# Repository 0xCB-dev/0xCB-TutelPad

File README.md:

# 0xcb-TutelPad
## An 8-key macropad with a 128x64 pixel OLED display

Licence | OSHWA
:-------------------------:|:-------------------------:
 | 

### Available here:

[KeebSupply](https://keeb.supply/products/0xcb-tutelpad)

### QMK

[keyboards/0xcb/tutelpad/](https://github.com/qmk/qmk_firmware/tree/master/keyboards/0xcb/tutelpad)

#### Flashing

* `qmk clone`
* `cd qmk_firmware`
* `export LTO=Y`
* Press switch 1 while plugging in to go into dfu mode (or the reset button)
* `make 0xcb/tutelpad:via:flash`

### Assembly:

You can use the [humanpnp](https://files.0xcb.dev/0xCB-TutelPad/humanpnp.html) to easily place components.

### PCB:
KiCad 6 stable release - using these [libs](https://github.com/0xCB-dev/0xcb-libs)

Top | Bottom
:-------------------------:|:-------------------------:
  |  

### CAD files:

[DXF](https://github.com/0xCB-dev/0xCB-TutelPad/tree/main/CAD/DXF)

#### BOM:
 References                        | Value          | Quantity | Part Nb.            
-----------------------------------|----------------|----------|---------------------
 SW1                               | SPST RA        | 1        | C115343             
 RGB4,RGB3,RGB2,RGB1               | WS2812B        | 4        | C114586             
 OL1                               | SSD1306-128x64 | 1        | amazon

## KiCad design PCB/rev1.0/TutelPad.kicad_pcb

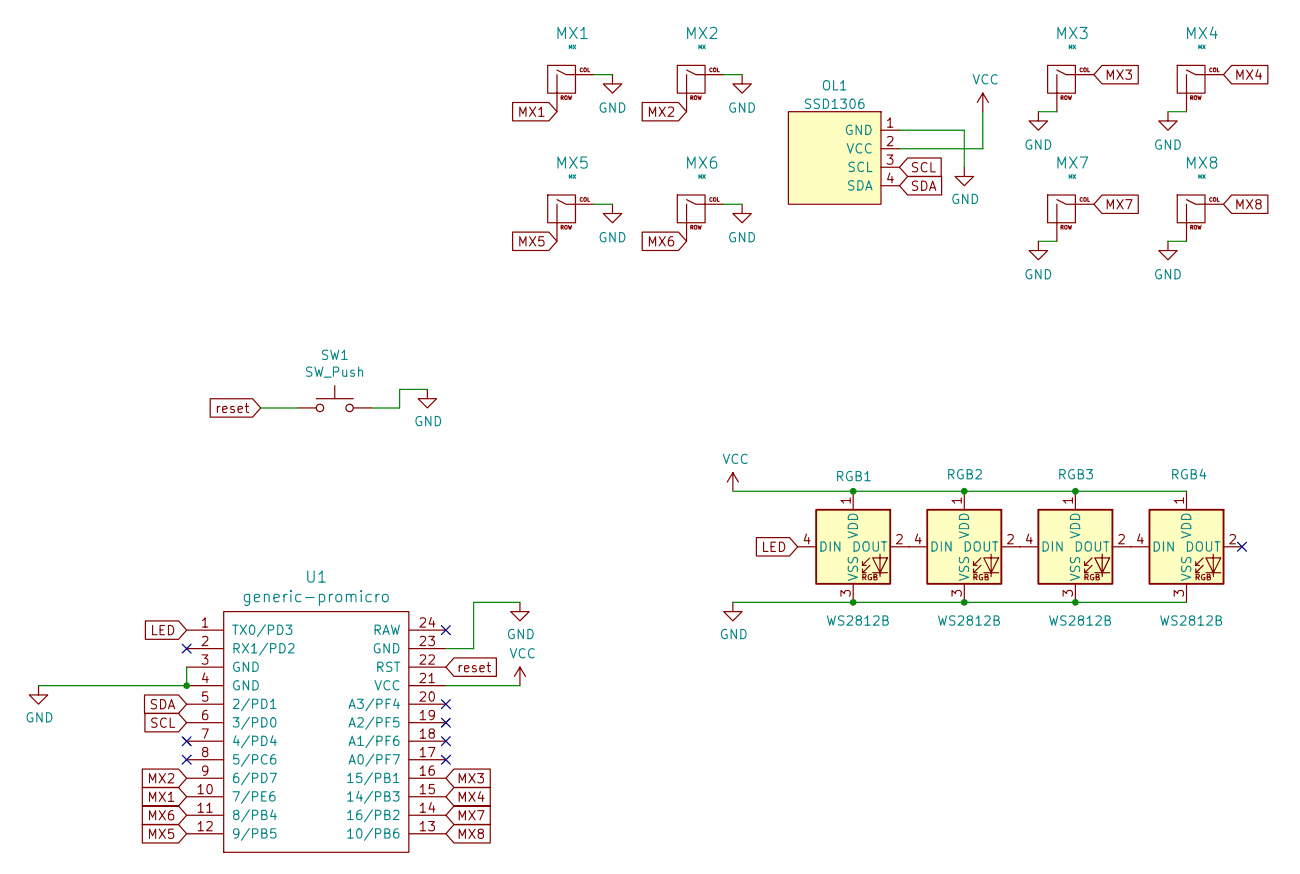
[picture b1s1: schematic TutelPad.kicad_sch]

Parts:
MX1, MX2, MX3, MX4, MX5, MX6, MX7, MX8: MX; SW_Cherry_MX_PCB_1.00u
OL1: SSD1306; 128x64OLED
RGB1, RGB2, RGB3, RGB4: WS2812B; LED_WS2812B_PLCC4_5.0x5.0mm_P3.2mm
SW1: SW_Push; SW_Tactile_SPST_Angled
U1: generic-promicro

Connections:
GND: MX1.1 (COL), MX2.1 (COL), MX3.2 (ROW), MX4.2 (ROW), MX5.1 (COL), MX6.1 (COL), MX7.2 (ROW), MX8.2 (ROW), OL1.1 (GND), RGB1.3 (VSS), RGB2.3 (VSS), RGB3.3 (VSS), RGB4.3 (VSS), SW1.2, U1.3 (GND), U1.4 (GND), U1.23 (GND)
LED: RGB1.4 (DIN), U1.1 (TX0/PD3)
MX1: MX1.2 (ROW), U1.10 (7/PE6)
MX2: MX2.2 (ROW), U1.9 (6/PD7)
MX3: MX3.1 (COL), U1.16 (15/PB1)
MX4: MX4.1 (COL), U1.15 (14/PB3)
MX5: MX5.2 (ROW), U1.12 (9/PB5)
MX6: MX6.2 (ROW), U1.11 (8/PB4)
MX7: MX7.1 (COL), U1.14 (16/PB2)
MX8: MX8.1 (COL), U1.13 (10/PB6)
unnamed: RGB1.2 (DOUT), RGB2.4 (DIN)
unnamed: RGB2.2 (DOUT), RGB3.4 (DIN)
unnamed: RGB3.2 (DOUT), RGB4.4 (DIN)
SCL: OL1.3 (SCL), U1.6 (3/PD0)
SDA: OL1.4 (SDA), U1.5 (2/PD1)
VCC: OL1.2 (VCC), RGB1.1 (VDD), RGB2.1 (VDD), RGB3.1 (VDD), RGB4.1 (VDD), U1.21 (VCC)
reset: SW1.1, U1.22 (RST)

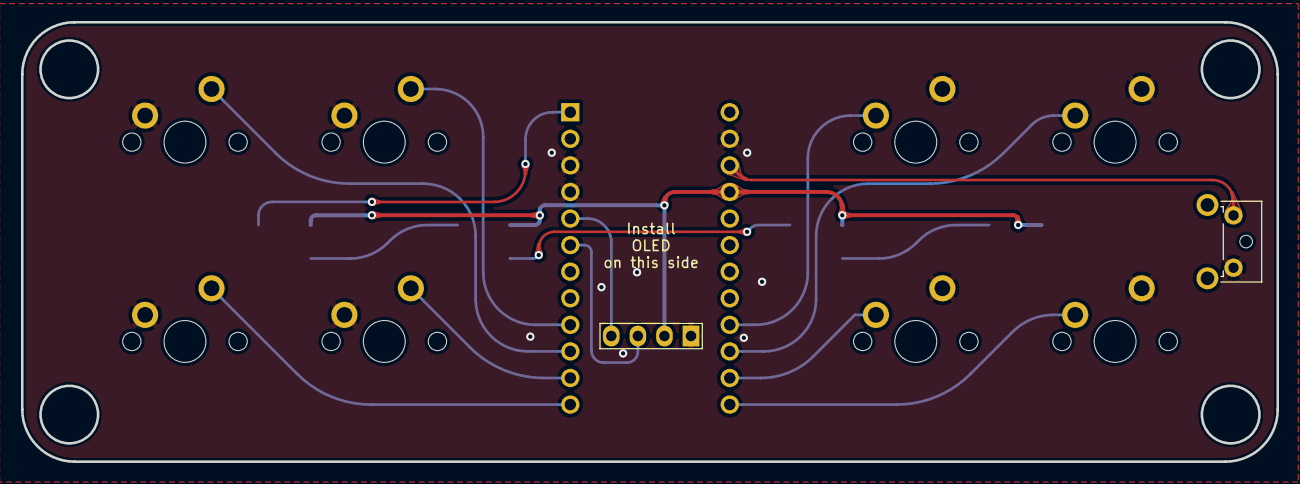
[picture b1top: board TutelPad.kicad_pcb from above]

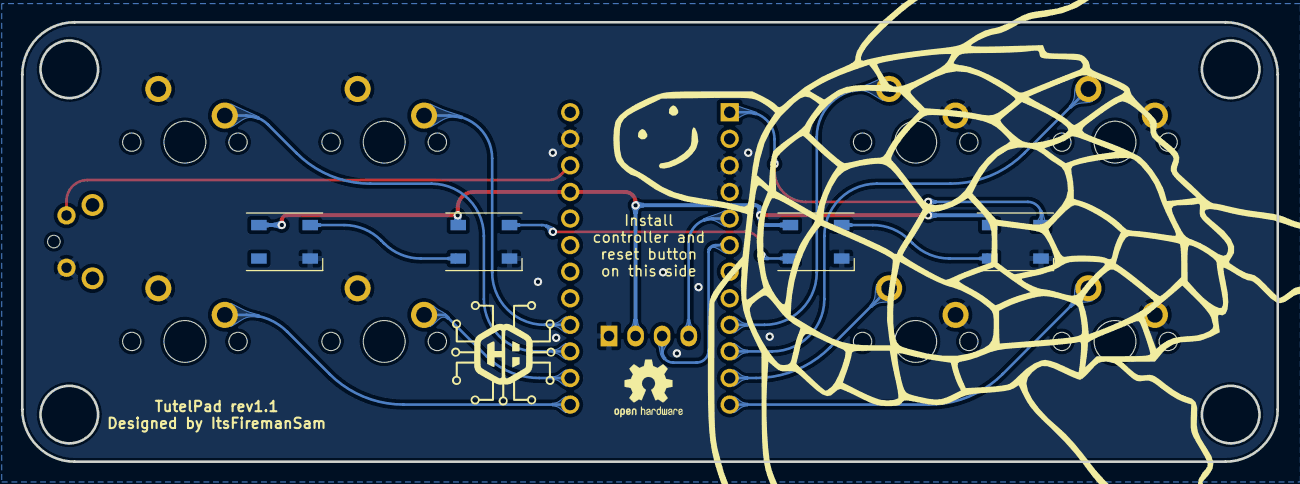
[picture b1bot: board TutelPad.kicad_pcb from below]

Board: 2 copper layers, 120.0 x 42.0 mm, 15 parts (4 on the bottom side), 17 nets.

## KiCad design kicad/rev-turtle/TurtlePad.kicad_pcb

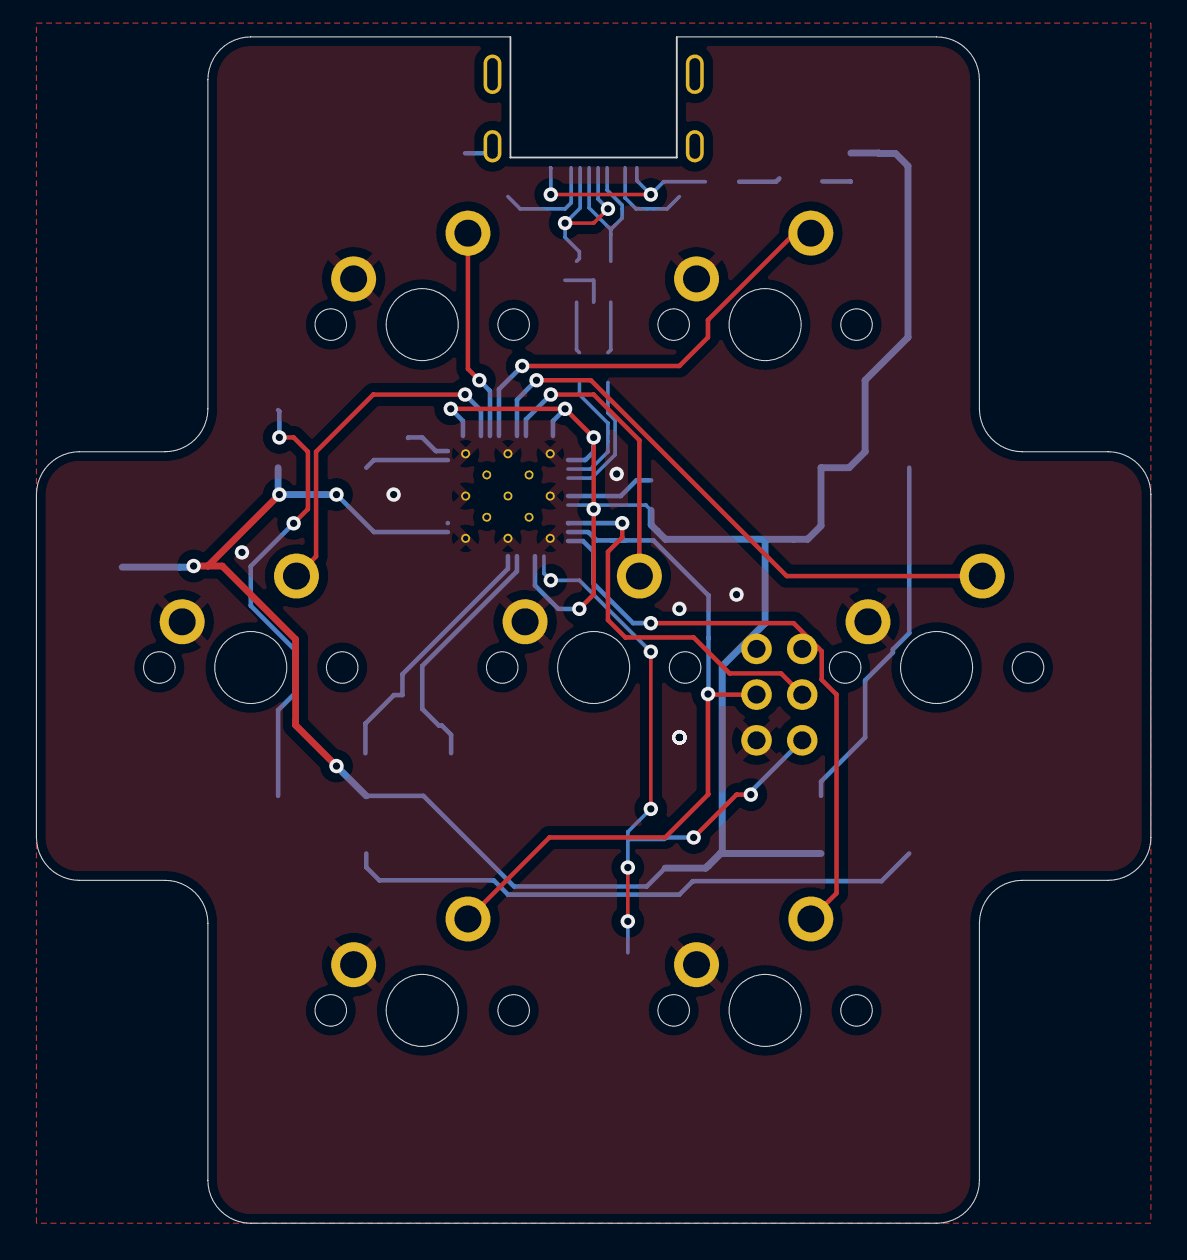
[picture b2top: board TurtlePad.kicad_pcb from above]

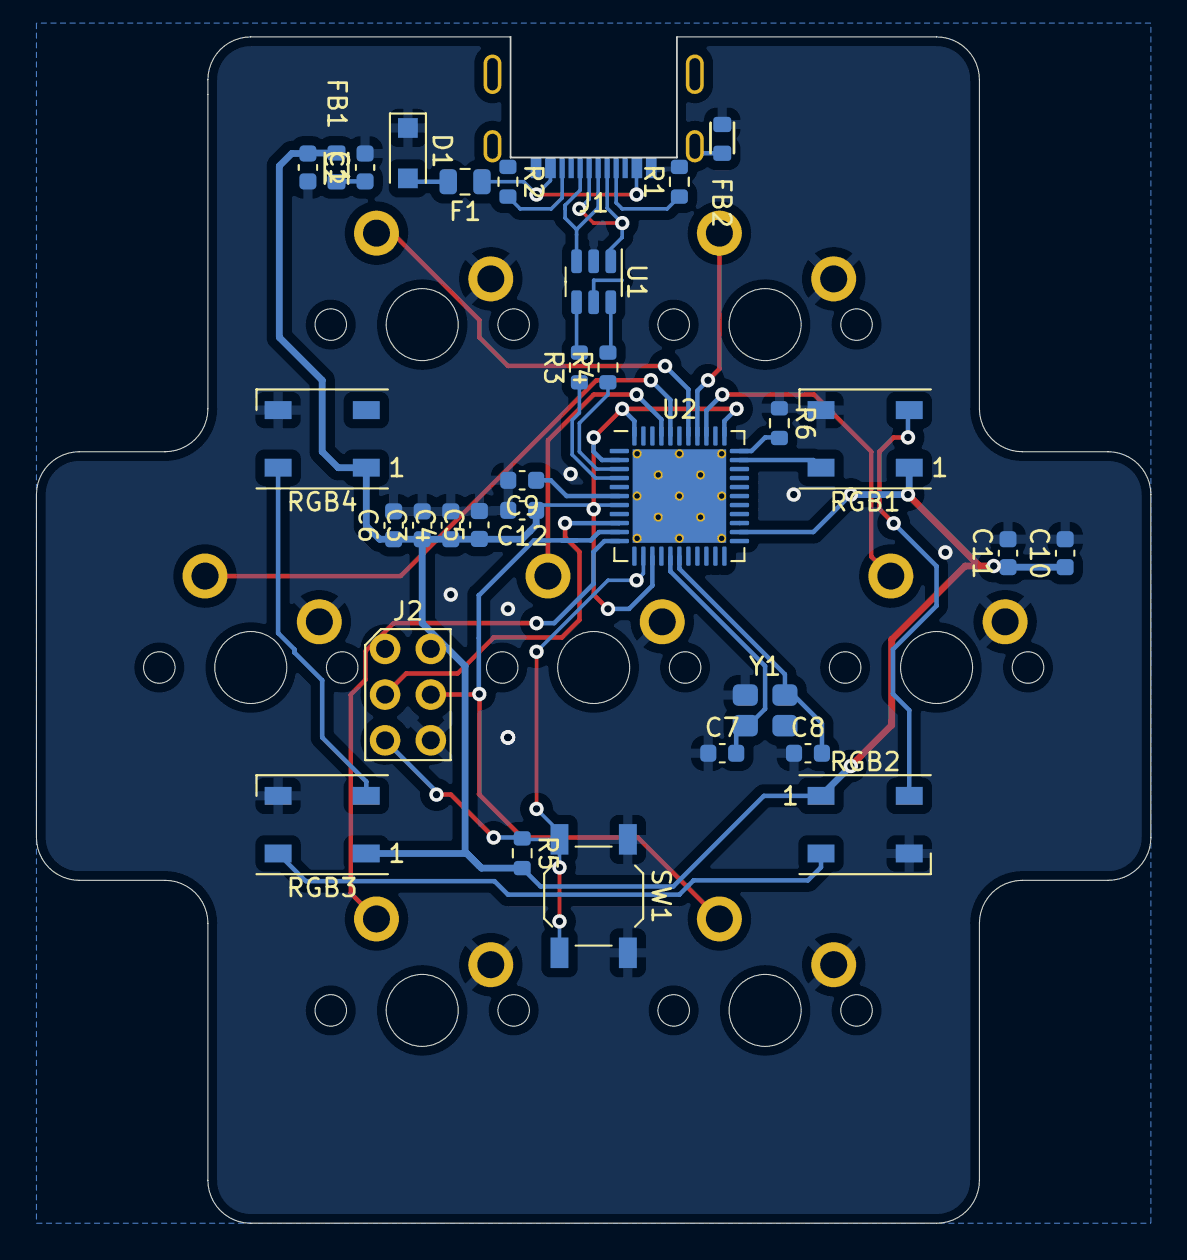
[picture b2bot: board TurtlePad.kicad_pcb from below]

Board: 2 copper layers, 61.9 x 65.9 mm, 39 parts (32 on the bottom side), 30 nets.

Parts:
C1: 10u; C_0603_1608Metric
C2, C6, C12: 1u; C_0603_1608Metric
C3, C4, C5, C9, C10, C11: 100n; C_0603_1608Metric
C7, C8: 22p; C_0603_1608Metric
D1: SMF5.0CA; D_SOD-123F
F1: 1A; Fuse_0805_2012Metric
FB1, FB2: 600R; Ferrite_Bead_0603
J1: USB_IN; molex2169900001
J2: AVR-ISP-6; AVR_PROG_2.54_THT
MX1, MX2, MX3, MX4, MX5, MX6, MX7: MX-NoLED; SW_Cherry_MX_PCB_1.00u
R1, R2: 5.1k; R_0603_1608Metric
R3, R4: 22; R_0603_1608Metric
R5, R6: 10k; R_0603_1608Metric
RGB1, RGB2, RGB3, RGB4: WS2812B; LED_WS2812B_PLCC4_5.0x5.0mm_P3.2mm
SW1: SW_Push; SW_SPST_TL3342
U1: USBLC6-2SC6; SOT-23-6
U2: ATMEGA32U4; QFN-44-1EP_7x7mm_P0.5mm_EP5.2x5.2mm_ThermalVias
Y1: 16MHz; Crystal_SMD_3225-4Pin_3.2x2.5mm

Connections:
/MCU+: R3.1, U2.4 (D+)
/MCU-: R4.1, U2.3 (D-)
/VBUS: F1.1, J1.A4 (VBUS), J1.A9 (VBUS), J1.B4 (VBUS), J1.B9 (VBUS), U1.5 (VBUS)
D+: R3.2, U1.4 (IO2)
D-: R4.2, U1.6 (IO1)
GND: C1.2, C2.2, C3.2, C4.2, C5.2, C6.2, C7.1, C8.1, C9.2, C10.2, C11.2, C12.2, D1.1 (A1), FB2.1, J1.A1 (GND), J1.A12 (GND), J1.B1 (GND), J1.B12 (GND), J2.6 (GND), MX1.1 (COL), MX2.1 (COL), MX3.1 (COL), MX4.1 (COL), MX5.1 (COL), MX6.1 (COL), MX7.1 (COL), R1.2, R2.1, R6.1, RGB1.3 (VSS), RGB2.3 (VSS), RGB3.3 (VSS), RGB4.3 (VSS), SW1.1, U1.2 (GND), U2.5 (UGnd), U2.15 (GND), U2.23 (GND), U2.35 (GND), U2.43 (GND), U2.45 (EP), Y1.2, Y1.4
LED: RGB1.4 (DIN), U2.32 (PC7)
MX1: MX1.2 (ROW), U2.37 (PF6)
MX2: MX2.2 (ROW), U2.38 (PF5)
MX3: MX3.2 (ROW), U2.36 (PF7)
MX4: MX4.2 (ROW), U2.41 (PF0)
MX5: MX5.2 (ROW), U2.40 (PF1)
MX6: J2.4 (MOSI), MX6.2 (ROW), U2.10 (PB2/MOSI)
MX7: J2.1 (MISO), MX7.2 (ROW), U2.11 (PB3/MISO)
unnamed: C1.1, D1.2 (A2), F1.2, FB1.1
unnamed: C7.2, U2.16 (XTAL1), Y1.1
unnamed: C8.2, U2.17 (XTAL2), Y1.3
unnamed: C9.1, U2.6 (UCap)
unnamed: FB2.2, J1.S1 (SHIELD)
unnamed: J1.A5 (CC1), R1.1
unnamed: J1.A6 (D+), J1.B6 (D+), U1.3 (IO2)
unnamed: J1.A7 (D-), J1.B7 (D-), U1.1 (IO1)
unnamed: J1.B5 (CC2), R2.2
unnamed: R6.2, U2.33 (PE2/~HWB)
unnamed: RGB1.2 (DOUT), RGB2.4 (DIN)
unnamed: RGB2.2 (DOUT), RGB3.4 (DIN)
unnamed: RGB3.2 (DOUT), RGB4.4 (DIN)
RST: J2.5 (~RST), R5.1, SW1.2, U2.13 (~RESET)
SCK: J2.3 (SCK), U2.9 (PB1/SCK), U2.20 (PD2)
VCC: C2.1, C3.1, C4.1, C5.1, C6.1, C10.1, C11.1, C12.1, FB1.2, J2.2 (VCC), R5.2, RGB1.1 (VDD), RGB2.1 (VDD), RGB3.1 (VDD), RGB4.1 (VDD), U2.2 (UVcc), U2.7 (VBus), U2.14 (VCC), U2.24 (AVCC), U2.34 (VCC), U2.44 (AVCC)

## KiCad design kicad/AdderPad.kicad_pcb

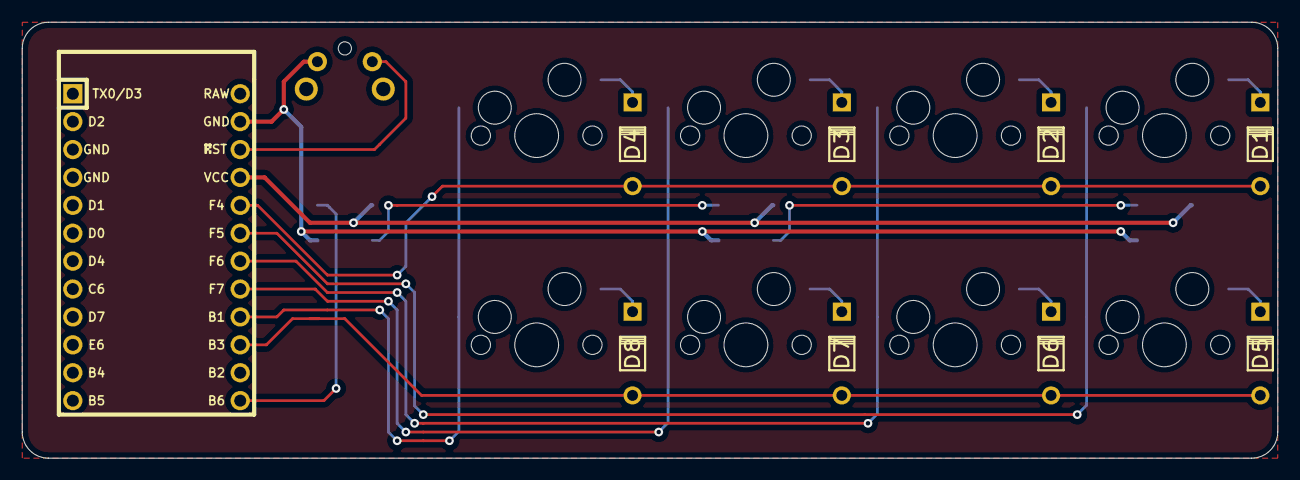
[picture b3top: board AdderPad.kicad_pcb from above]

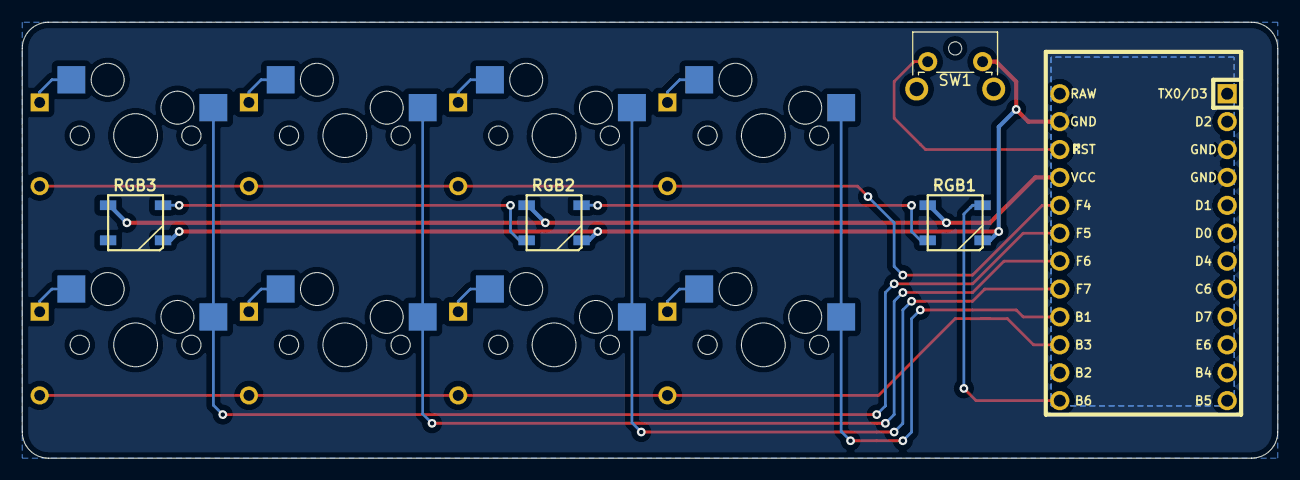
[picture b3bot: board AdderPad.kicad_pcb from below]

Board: 2 copper layers, 114.3 x 39.7 mm, 21 parts (4 on the bottom side), 20 nets.

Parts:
D1, D2, D3, D4, D5, D6, D7, D8: D_Small; Diode
MX1, MX2, MX3, MX4, MX5, MX6, MX7, MX8: MX-NoLED; MXOnly-1U-Hotswap
RGB1, RGB2, RGB3: WS2812B
SW1: SW_Push; SW_Tactile_SPST_Angled_MJTP1117
U1: ProMicro; ArduinoProMicro

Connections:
COL0: MX1.1, MX5.1, U1.19
COL1: MX2.1, MX6.1, U1.18
COL2: MX3.1, MX7.1, U1.17
COL3: MX4.1, MX8.1, U1.16
GND: RGB1.3, RGB2.3, RGB3.3, SW1.2, U1.3, U1.4, U1.23
LED: RGB1.4, U1.13
unnamed: D1.2, MX1.2
unnamed: D2.2, MX2.2
unnamed: D3.2, MX3.2
unnamed: D4.2, MX4.2
unnamed: D5.2, MX5.2
unnamed: D6.2, MX6.2
unnamed: D7.2, MX7.2
unnamed: D8.2, MX8.2
unnamed: RGB1.2, RGB2.4
unnamed: RGB2.2, RGB3.4
ROW0: D1.1, D2.1, D3.1, D4.1, U1.20
ROW1: D5.1, D6.1, D7.1, D8.1, U1.15
VCC: RGB1.1, RGB2.1, RGB3.1, U1.21
reset: SW1.1, U1.22

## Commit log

2021-12-19 Initialize project
2021-12-19 Add footprint submodule
2021-12-19 Add keebio components
2021-12-19 Added libraries, fixed folder structure
2021-12-19 Finished PCB
2021-12-21 Added angled reset button
2021-12-21 Added RGB underglow LEDs
    Rerouted traces, new mill sizes
2021-12-21 Multiple updates
    - added 128x64 OLED support
    - added fourth underglow RGB
    - resize PCB
2021-12-21 Repositioned
2021-12-21 Rename project to TurtlePad
2021-12-21 Final name changes
2021-12-22 fixed some minor stuff, updated the outline, added solidworks folder for DXFs
2021-12-23 Added switch plate and backplate folders
2021-12-30 plates and prod files
2022-01-17 Restructuring
2022-01-17 First revision build guide
2022-01-22 Started work on rev1.1
2022-01-22 Fix filling
2022-01-25 Added designer silkscreen
2022-02-09 rev1.1 again
2022-02-09 cleaned up, rounded traces added teardrops
2022-02-09 Placed all surface mount parts for now
    Just need to figure out how in God's name to route all of it
2022-02-09 Revert "Placed all surface mount parts for now"
    This reverts commit df8ecd82c21d147e971f6b322fb3575a65e4f200.
2022-02-09 Revert "Revert "Placed all surface mount parts for now""
    This reverts commit 42bec52487df9ac41952cb28762131b75d3db880.
2022-02-10 Redid schematic because I am an idiot
2022-02-10 Placed and routed all components on PCB
2022-02-10 PCB edge and copper fill
2022-03-03 Fix LED without GND
2022-03-06 plates
2022-03-13 changed PCB, added switch and bottom plate, added gerbers
2022-04-09 TutelPad transformation
    Updated the silkscreen, renamed all files to TutelPad, renamed rev1.1 to rev1.0
2022-04-09 silkscreen on switch and backplate
2022-04-15 cleaned repo and changed libs
2022-04-15 fixing the readme
2022-04-15 pointed links
2022-04-15 fixed image
2022-05-04 OSHW
2022-05-04 fixed board outline
2022-08-24 git update
2022-08-24 git update 2
2022-08-24 git update 3
